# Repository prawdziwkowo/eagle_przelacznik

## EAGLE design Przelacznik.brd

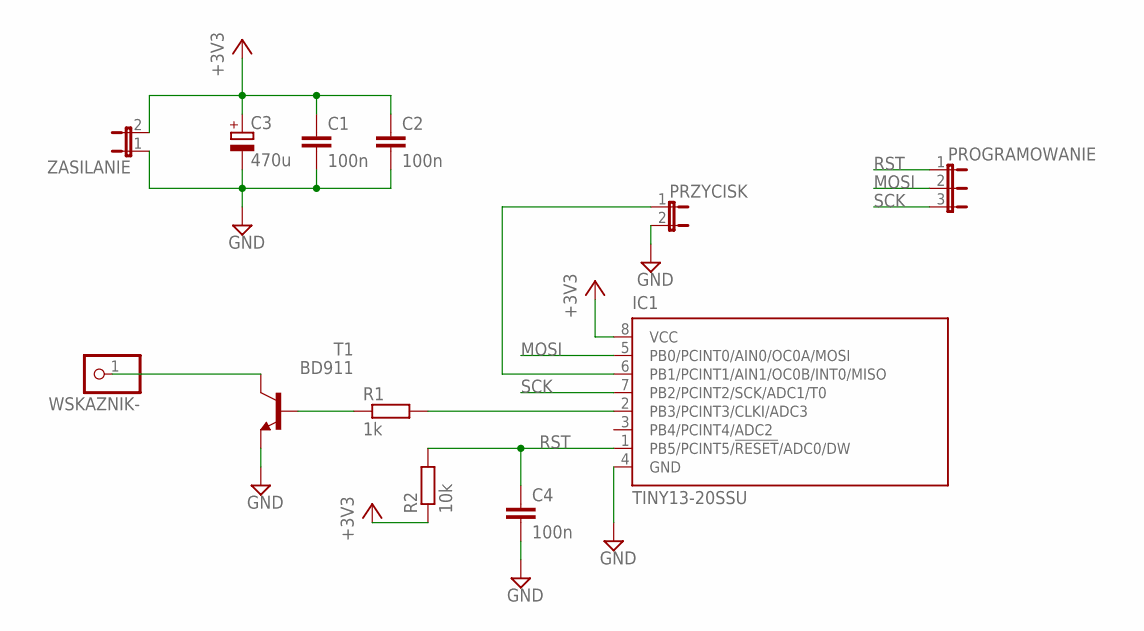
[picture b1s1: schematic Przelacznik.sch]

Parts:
C1, C4: 100n; C025-024X044
C2: 100n; C0805
C3: 470u; E3,5-8
IC1: TINY13-20SSU; 8S1
PROGRAMOWANIE: JP2E; JP2
PRZYCISK: JP1E; JP1
R1: 1k; 0411/12
R2: 10k; 0411/12
T1: BD911; TO220
WSKAZNIK-: PINHD-1X1; 1X01
ZASILANIE: JP1E; JP1

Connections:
+3V3: C1.1, C2.1, C3.+, IC1.8 (VCC), R2.1, ZASILANIE.2
GND: C1.2, C2.2, C3.-, C4.2, IC1.4 (GND), PRZYCISK.2, T1.3 (E), ZASILANIE.1
MOSI: IC1.5 (PB0/PCINT0/AIN0/OC0A/MOSI), PROGRAMOWANIE.2
unnamed: T1.2 (C), WSKAZNIK-.1
unnamed: R1.1, T1.1 (B)
unnamed: IC1.2 (PB3/PCINT3/CLKI/ADC3), R1.2
unnamed: IC1.6 (PB1/PCINT1/AIN1/OC0B/INT0/MISO), PRZYCISK.1
RST: C4.1, IC1.1 (PB5/PCINT5/!RESET!/ADC0/DW), PROGRAMOWANIE.1, R2.2
SCK: IC1.7 (PB2/PCINT2/SCK/ADC1/T0), PROGRAMOWANIE.3

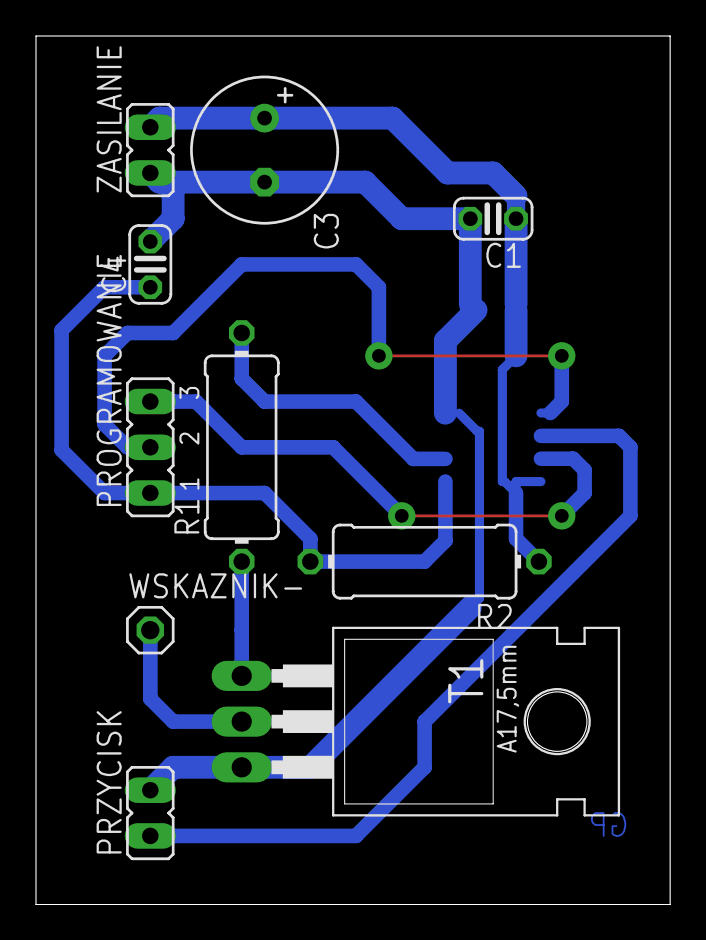
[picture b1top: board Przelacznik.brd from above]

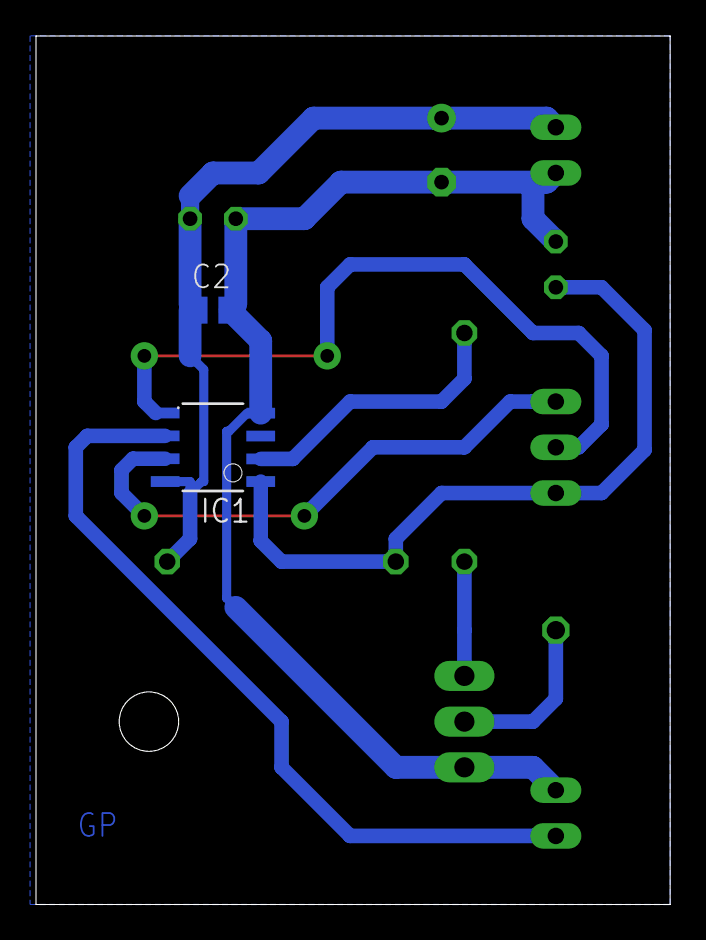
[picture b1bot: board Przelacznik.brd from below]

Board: 2 copper layers, 35.2 x 48.2 mm, 12 parts (2 on the bottom side), 9 nets.

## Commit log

2018-02-19 przelacznik schemat i plytka
